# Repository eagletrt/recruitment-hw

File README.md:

# Recruitment for E-Agle TRT | Electronics division

Welcome to the recruitment *test* for the electronics team of E-Agle Trento Racing Team.

This test gives us an initial understanding of applicants' abilities without the pressure of a formal exam.

It also introduces you to the tools we use, so you can get up to speed with the team's workflow before you need to use them under pressure.

You will be assigned a task after our first meeting, during which we introduce the team and the electronics division. **Do not start until we tell you to.**

To better understand the task and the competition's structure, we strongly recommend reading the latest rulebook, available on the [Formula Student Germany rules page](https://www.formulastudent.de/fsg/rules).

## What we'll look into

- Schematic quality: clear connections, consistent labels, tidy organisation into functional blocks and good KiCad practices.
- Circuit correctness: operation that meets the requirements, suitable components and calculations that support the design.
- Technical reasoning: clear explanations of the circuit architecture, component choices and sizing that demonstrate your understanding.
- Documentation quality: clear and complete explanations, calculations and verification, consistent with the submitted schematic.
- `git` usage: fork, branch, clone, commit, push, pull.

## General instructions

- You may use AI tools to help you understand concepts, but you must design the circuit, draw the schematic, carry out the calculations and write the documentation yourself. Any submitted work found to be AI-generated, or that you cannot explain when asked, will result in disqualification and your application will not be considered. Practices that demonstrate your authorship, such as meaningful progress commits and notes explaining your design decisions, will be appreciated.
- Create a repository on your GitHub account and copy this project into it. If you do not have an account, create one. **Do not clone this repository!**
- Use the existing KiCad project for your assigned task as a starting point, or create a new one.
- Create a branch named `name_surname` from `master` and commit your progress on that branch.
- Commit your progress throughout the assignment. **Do not commit only the finished project.**
- When you are done, export the schematic inside `docs/`.
- Export a bill of materials (BOM) from KiCad as a CSV file inside `docs/`. Include component references, quantities, values, manufacturers, manufacturer part numbers and Mouser part numbers or product links.
- Include a short explanation of the circuit, component choices and calculations inside `docs/`, together with annotated timing diagrams or simulations covering the operating cases required by your assigned task. Simulations are not mandatory; explain how the schematic produces the expected behaviour.
- If you also design a PCB, export the production Gerber files inside `output/`.
- If you have not already done so, submit your [application form](https://eagletrt.it/apply).
- If you have questions, contact [electronics@eagletrt.it](mailto:electronics@eagletrt.it).
- You can also visit our lab on floor -2 of Povo 2 if we are slow to reply.
- You have **2 weeks (14 days)** to work on this project. **This is a firm deadline; meeting it is part of the assessment.**

## Links

- [Website](https://www.eagletrt.it)
- [Instagram](https://www.instagram.com/eagletrt)
- [LinkedIn](https://www.linkedin.com/company/eagletrentoracingteam)

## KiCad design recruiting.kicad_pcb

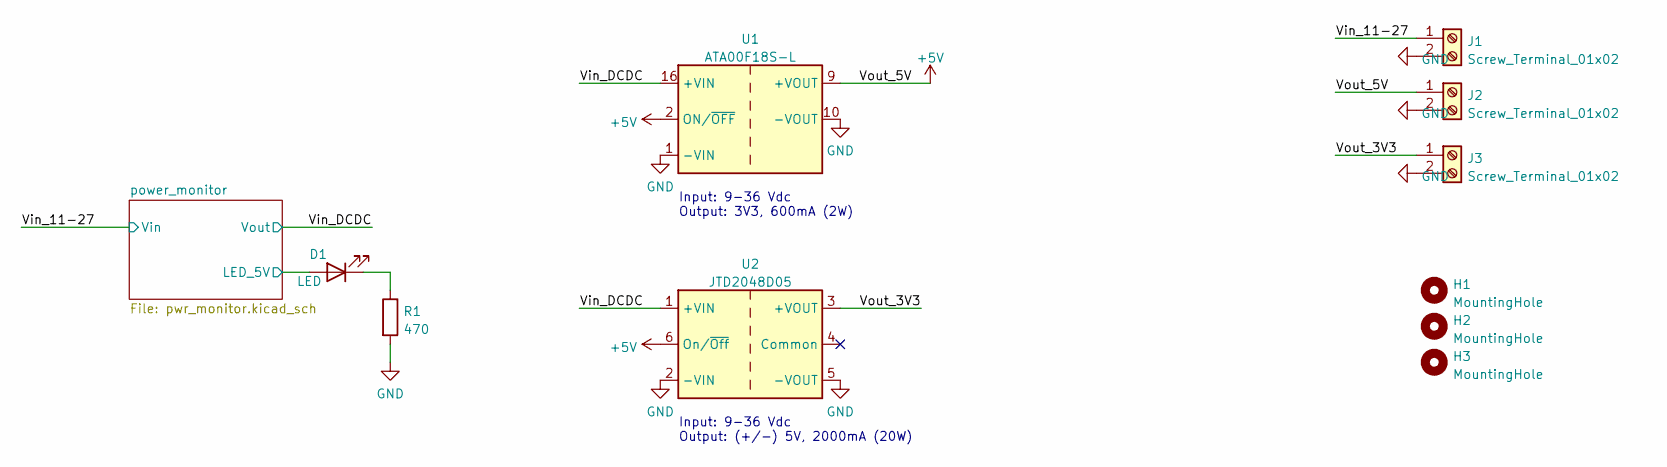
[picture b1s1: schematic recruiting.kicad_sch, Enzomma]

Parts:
D1: LED; LED_1206_3216Metric
H1, H2, H3: MountingHole; MountingHole_2mm
J1, J2, J3: Screw_Terminal_01x02; TerminalBlock_4Ucon_1x02_P3.50mm_Horizontal
R1: 470; R_1206_3216Metric
U1: ATA00F18S-L; Converter_DCDC_Artesyn_ATA_SMD
U2: JTD2048D05; Converter_DCDC_XP_POWER_JTDxxxxxxx_THT

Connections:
+5V: J2.1, U1.2 (ON/~OFF), U1.9 (+VOUT), U2.6 (On/~Off); also elsewhere on the board
/Vin_11-27: J1.1; also elsewhere on the board
/Vin_DCDC: U1.16 (+VIN), U2.1 (+VIN); also elsewhere on the board
/Vout_3V3: J3.1, U2.3 (+VOUT)
/power_monitor/LED_5V: D1.2 (A); also elsewhere on the board
GND: J1.2, J2.2, J3.2, R1.2, U1.1 (-VIN), U1.10 (-VOUT), U2.2 (-VIN), U2.5 (-VOUT); also elsewhere on the board
unnamed: D1.1 (K), R1.1

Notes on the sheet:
Input: 9-36 Vdc Output: (+/-) 5V, 2000mA (20W)
Input: 9-36 Vdc Output: 3V3, 600mA (2W)

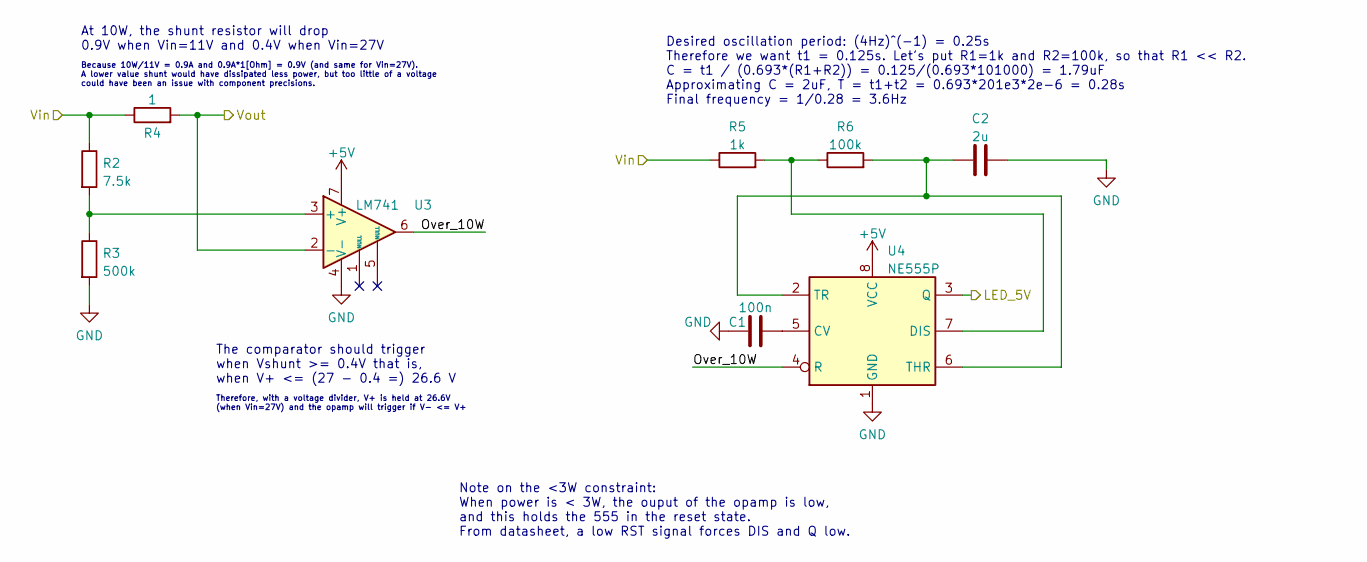
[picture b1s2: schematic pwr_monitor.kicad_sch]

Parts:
C1: 100n; CP_Elec_3x5.3
C2: 2u; C_Axial_L3.8mm_D2.6mm_P7.50mm_Horizontal
R2: 7.5k; R_1206_3216Metric
R3: 500k; R_1206_3216Metric
R4: 1; R_1206_3216Metric
R5: 1k; R_1206_3216Metric
R6: 100k; R_1206_3216Metric
U3: LM741; DIP-8-16_W7.62mm
U4: NE555P; DIP-8_W7.62mm

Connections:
+5V: U3.7 (V+), U4.8 (VCC); also elsewhere on the board
/Vin_11-27: R2.1, R4.1, R5.1; also elsewhere on the board
/Vin_DCDC: R4.2, U3.2 (-); also elsewhere on the board
/power_monitor/LED_5V: U4.3 (Q); also elsewhere on the board
/power_monitor/Over_10W: U3.6, U4.4 (R)
GND: C1.2, C2.2, R3.2, U3.4 (V-), U4.1 (GND); also elsewhere on the board
unnamed: C1.1, U4.5 (CV)
unnamed: C2.1, R6.2, U4.2 (TR), U4.6 (THR)
unnamed: R2.2, R3.1, U3.3 (+)
unnamed: R5.2, R6.1, U4.7 (DIS)

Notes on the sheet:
Because 10W/11V = 0.9A and 0.9A*1[Ohm] = 0.9V (and same for Vin=27V). A lower value shunt would have dissipated less power, but too little of a voltage could have been an issue with component precisions.
Desired oscillation period: (4Hz)^(-1) = 0.25s Therefore we want t1 = 0.125s. Let's put R1=1k and R2=100k, so that R1 << R2. C = t1 / (0.693*(R1+R2)) = 0.125/(0.693*101000) = 1.79uF Approximating C = 2uF, T = t1+t2 = 0.693*201e3*2e-6 = 0.28s Final frequency = 1/0.28 = 3.6Hz
Note on the <3W constraint: When power is < 3W, the ouput of the opamp is low, and this holds the 555 in the reset state. From datasheet, a low RST signal forces DIS and Q low.
At 10W, the shunt resistor will drop 0.9V when Vin=11V and 0.4V when Vin=27V
The comparator should trigger when Vshunt >= 0.4V that is, when V+ <= (27 - 0.4 =) 26.6 V
Therefore, with a voltage divider, V+ is held at 26.6V (when Vin=27V) and the opamp will trigger if V- <= V+

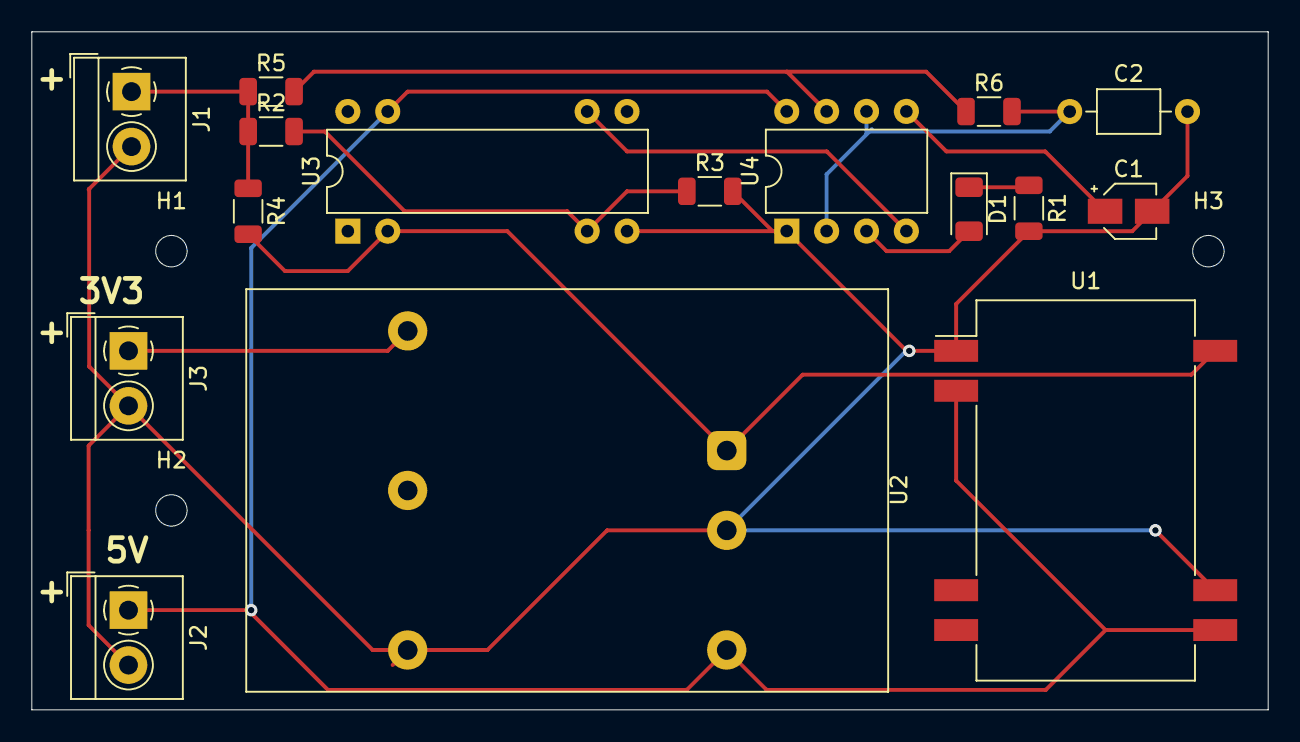
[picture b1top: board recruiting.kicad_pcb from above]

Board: 2 copper layers, 78.7 x 43.2 mm, 19 parts (0 on the bottom side), 12 nets.

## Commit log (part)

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2022-05-02 fatti alcuni calcoli secondo datasheet per il dimensionamento delle resistenze Rfb1/2 e dimensionamento del MOSFET a canale P per lo switch
2022-05-02 ALCUNE MODIFICHE AL CIRCUITO
2022-05-04 aggiunta di un file che esplicita alcuni calcoli
2022-05-09 aggiornato il foglio di calcolo per il dimensionamento dell'alimentatore
2022-05-24 alcune modifiche ai package di alcuni componenti e continuazione del design del circuito stampato
2022-06-07 completato il file pcb, creato un file gerber nella directory 'output' e creato i file pdf dello schema nella directory 'docs'
2022-06-08 condensatori riposizionati
2022-09-06 Add project
2022-09-12 modificalo lo schematic e rifatto in parte il design PCB
2022-09-12 ultimi dettagli al pcb
2022-11-03 Add hierarchical sheet with power monitor
2022-11-04 Add op-amp for power monitoring
2022-11-05 Add NE555 to blink LED at 3.5Hz
2022-11-05 Finish power monitor
2022-11-05 Create PCB
2022-11-05 Export circuit to gerber and PDF
